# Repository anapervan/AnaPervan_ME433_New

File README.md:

Ana Pervan
March 28, 2017

This repository is for the ME 433 class. It will include homeworks, the final project, and maybe other stuff

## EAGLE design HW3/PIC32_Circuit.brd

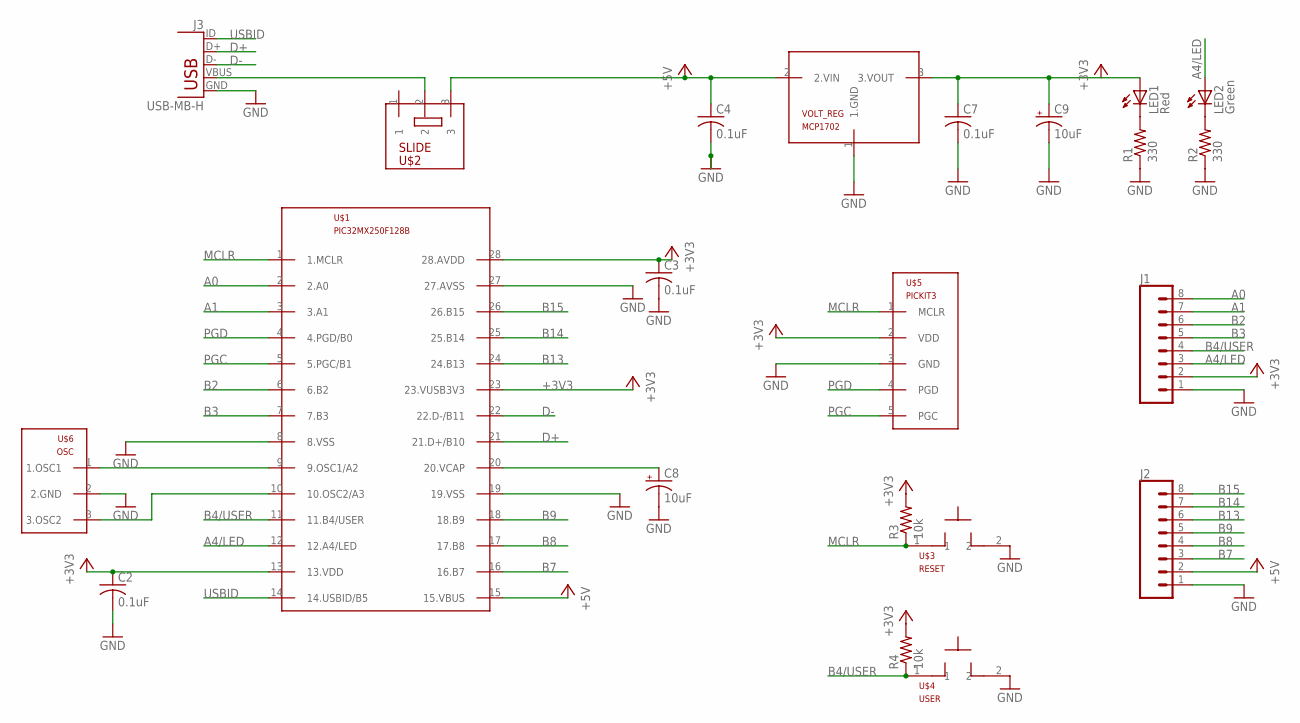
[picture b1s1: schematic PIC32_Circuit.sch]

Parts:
C2, C3, C4, C7: 0.1uF; C025-050X050
C8, C9: 10uF; B45181B
J1, J2: CONN_08"; 1X08
J3: USB-MB-H
LED1: Red; LED3MM
LED2: Green; LED3MM
R1, R2: 330; 0207/10
R3, R4: 10k; 0207/10
U$1: PIC32MX250F128B; DIL28-3
U$2: SLIDE
U$3: RESET; PB
U$4: USER; PB
U$5: PICKIT3; 1X05
U$6: OSC
VOLT_REG: MCP1702; TO92

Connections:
+3V3: C2.1, C3.1, J1.2, R3.2, R4.2, U$1.13 (13.VDD), U$1.23 (23.VUSB3V3), U$1.28 (28.AVDD), U$5.2 (VDD)
+5V: C4.1, J2.2, U$1.15 (15.VBUS), U$2.3, VOLT_REG.2 (2.VIN)
A0: J1.8, U$1.2 (2.A0)
A1: J1.7, U$1.3 (3.A1)
A4/LED: J1.3, LED2.A, U$1.12 (12.A4/LED)
B2: J1.6, U$1.6 (6.B2)
B3: J1.5, U$1.7 (7.B3)
B4/USER: J1.4, R4.1, U$1.11 (11.B4/USER), U$4.1
B7: J2.3, U$1.16 (16.B7)
B8: J2.4, U$1.17 (17.B8)
B9: J2.5, U$1.18 (18.B9)
B13: J2.6, U$1.24 (24.B13)
B14: J2.7, U$1.25 (25.B14)
B15: J2.8, U$1.26 (26.B15)
D+: J3.D+, U$1.21 (21.D+/B10)
D-: J3.D-, U$1.22 (22.D-/B11)
GND: C2.2, C3.2, C4.2, C7.2, C8.-, C9.-, J1.1, J2.1, J3.GND, R1.1, R2.1, U$1.8 (8.VSS), U$1.19 (19.VSS), U$1.27 (27.AVSS), U$3.2, U$4.2, U$5.3 (GND), U$6.2 (2.GND), VOLT_REG.1 (1.GND)
MCLR: R3.1, U$1.1 (1.MCLR), U$3.1, U$5.1 (MCLR)
unnamed: LED1.K (C), R1.2
unnamed: LED2.K (C), R2.2
unnamed: C7.1, C9.+, LED1.A, VOLT_REG.3 (3.VOUT)
unnamed: U$1.10 (10.OSC2/A3), U$6.3 (3.OSC2)
unnamed: U$1.9 (9.OSC1/A2), U$6.1 (1.OSC1)
unnamed: C8.+, U$1.20 (20.VCAP)
PGC: U$1.5 (5.PGC/B1), U$5.5 (PGC)
PGD: U$1.4 (4.PGD/B0), U$5.4 (PGD)
USBID: J3.ID, U$1.14 (14.USBID/B5)
VBUS: J3.VBUS, U$2.2

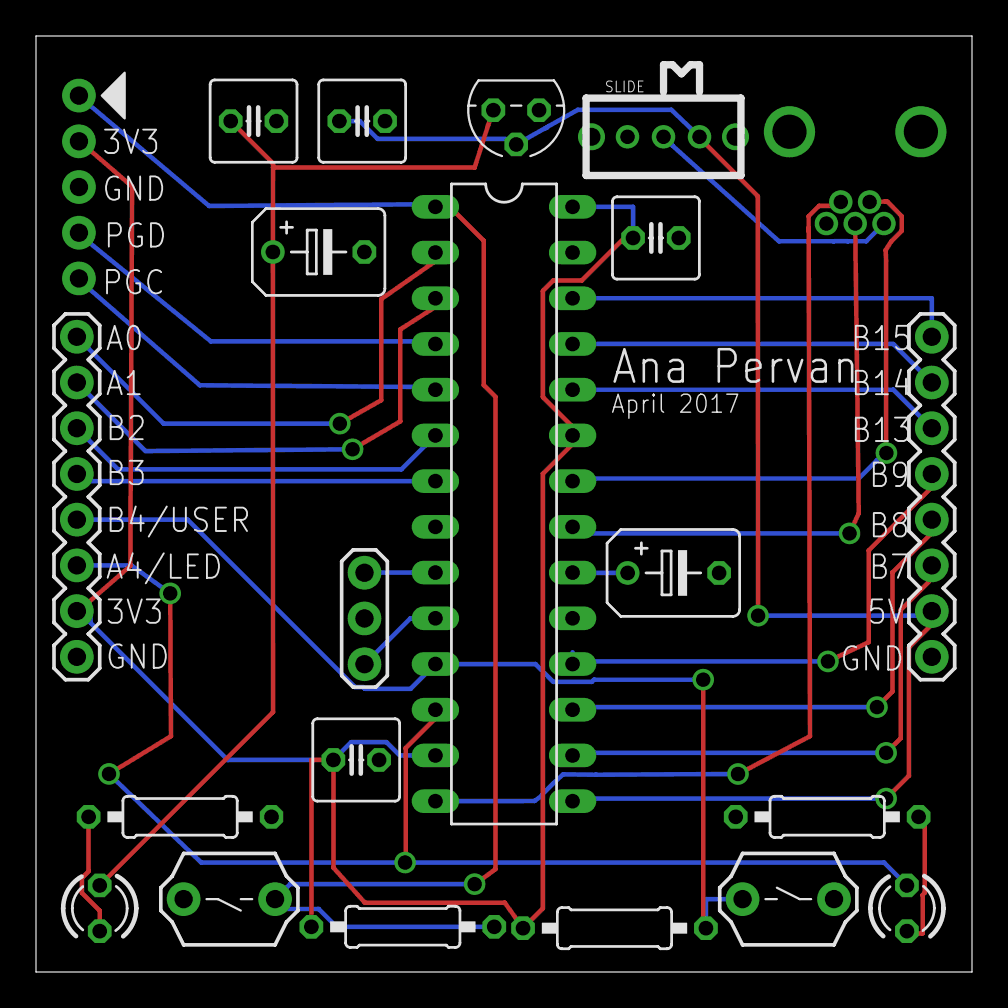
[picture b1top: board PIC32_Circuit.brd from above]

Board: 2 copper layers, 52.0 x 52.0 mm, 22 parts (0 on the bottom side), 28 nets.

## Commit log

2017-03-28 :space_invader: Added .gitattributes & .gitignore files
2017-03-28 My first commit!
2017-03-29 Created new main code
2017-03-29 Screenshots/Photos Added
2017-03-29 Updated #pragma's
2017-03-29 green LED turns on
2017-03-29 Finished HW1
    Added LED blinking at 1kHz and pushbutton code
2017-03-29 Photo of Circuit Diagram
2017-03-30 Moved files into a folder
2017-04-04 .lbr, .sch, and .brd
    Made a library of components, drew the schematic, and started the board
    layout
2017-04-05 Board v1
    Added all wires, still need to check errors
2017-04-06 Final Board
2017-04-07 Final .brd and gerber files
2017-04-10 Started work on HW4
2017-04-11 Progress on HW4
    still not working though
2017-04-11 Finished Homework 4
    And added DAC output screenshot
2017-04-12 Changed name and added circuit diagram
2017-04-13 Working on Homework 5
2017-04-13 Still Working on Homework 5
2017-04-13 Homework 5 Completed
2017-04-13 Added Circuit Diagram
2017-04-16 Started Homework 6
2017-04-18 Progress on Homework 6
2017-04-21 Finished HW 6
2017-04-22 Finished HW7
2017-04-26 Finished Homework 8
2017-04-26 Working on Homework 9
    Nick's code is working
2017-04-26 Progress on Homework 9
    reads r and prints Hello, with no r and no numbers
2017-04-27 Finished Homework 9
2017-05-11 Finished HW10
2017-05-11 Working on HW11
2017-05-12 Working on Homework 11
2017-05-15 Worked on Android
2017-05-16 Finished HW12
2017-05-17 HW13 - got it capturing the green surfaces
    still need to add slider
2017-05-17 Finished HW13
2017-05-17 HW13 Video
2017-05-19 Box and Wheel CAD drawings
2017-05-22 CAD updates
2017-05-22 Box Photos
2017-06-02 Working on final project
2017-06-05 Tech Cup CAD files done
2017-06-05 new top dimensions
2017-06-06 updated wheels and motor cover cad
2017-06-07 hw16
2017-06-08 tech cup work
2017-06-08 HW 14 Video
2017-06-08 working on android usb
2017-06-08 android usb app working
2017-06-08 video
2017-06-08 HW19 Image Processing App working
    called New
2017-06-08 the motors move and respond to inputs in the terminal!
2017-06-08 HW18 working version
2017-06-08 merging codes - updated pic code
2017-06-08 Tech Cup working!!
    (well enough)
    Android code is on HW14
2017-06-08 uploading videos
